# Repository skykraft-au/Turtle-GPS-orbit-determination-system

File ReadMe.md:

# Overview
The Turtle GPS is an open-source, cost-effective, low-power, and low-weight solution to orbit determination. The device resolves the issues faced by standard tracking methods such as radar while democratising space by making tracking cooperative and community-based. The device satisfies CoCom regulations by being post-processed and non-continuous; instead, it beacons GPS data over LoRa packets at specified intervals.

The device is highly configurable through the FPGA Verilog code; see the configuration section below for more information.

Further development on the device is needed; the community is welcome to contribute to this. Information on directions for this development can be found in the Todo section below.

## Note regarding Turtle GPS v2.0
Note that the Turtle GPS v2.0 does not work by default, as there are issues regarding the flash and power supply components on the board; these issues are resolved in version 2.1. If you wish to use version 2.0, you will need to resolve these issues. The key issues and solutions are as follows:
- There are missing pull-up resistors on pins 1, 3, and 7 of the Flash memory; these should be 10 kΩ.
- The pull-up resistors on the M0, M1, and M2 pins on the underside of the FPGA are 10 kΩ, but they should be 1 kΩ to initiate the correct startup configuration.
- A few issues exist in the lower half of the power supply, including incorrect placement of the boost converter, sensitive output of the first 3.3 V LDO, and insufficient current rating in both the diode and boost converter. To resolve this, I recommend bypassing this section by powering the board with 3.3 V through test point 3.
- The done indicator pin from the FPGA should be a pull-up and not a pull-down.

# Todo
- GPS v2.1: Resolve issues with v2.0, update FPGA clock to an LVCMOS TCXO, tune LoRa RF path to between 401 MHz and 403 MHz.
- Update code to default the LoRa frequency to 401 MHz to 403 MHz and cascade the FIR to allow for a sharper cutoff to be attained with the limited FPGA resources.
- Program LoRa receiving capabilities into the FPGA to allow for remote shutdown with a unique user-defined code.
- Optimise size, weight, and performance of the device
- Test in orbit
- Set up a public website for uploading and processing of data
- Add satellite ID code generator and logger to the website

# Configuration of the Device
By default, the packets transmitted over LoRa are 512 bits wide and include a unique, user-defined satellite ID Code, packet index, user-defined bits, and the actual data.
| Number of Bits | Bit Locations | Purpose |
| -------------- | ------------- | ------- |
| 24 | \[512:489\] | Satellite ID Code |
| 12 | \[488:477\] | Packet Index |
| 28 | \[476:449\] | User-defined bits |
| 448 | \[448:0\] | GPS IQ Data |

The user-defined bits can be configured by changing the value of the respective register in the Verilog code. The configuration of the MAX2771 GNSS Receiver and the LoRa SX1276 can be changed by adjusting the values of their respective configuration registers in the MAX_Driver and LORA_Driver Verilog modules, respectively.

The total transmission size, as well as the sample size and whether samples are continuous or not, can all be configured through the value of the GPS_Config register in the GPS_Top Verilog module. Comments are included in the code to assist users with this.

# Licensing

This repository contains material under multiple licenses.

## Hardware

The hardware design files are licensed under CERN-OHL-P v2.

This includes:
- GPS v2.0/KiCad PCB/

## HDL and Software

The HDL and software source code are licensed under the MIT License.

This includes:
- GPS v2.0/Software and HDL/

## Documentation

Documentation, diagrams, and images are licensed under
Creative Commons Attribution 4.0 International (CC BY 4.0).

This includes:
- GPS v2.0/BoM/

A copy of each license is available in the licenses/ directory.

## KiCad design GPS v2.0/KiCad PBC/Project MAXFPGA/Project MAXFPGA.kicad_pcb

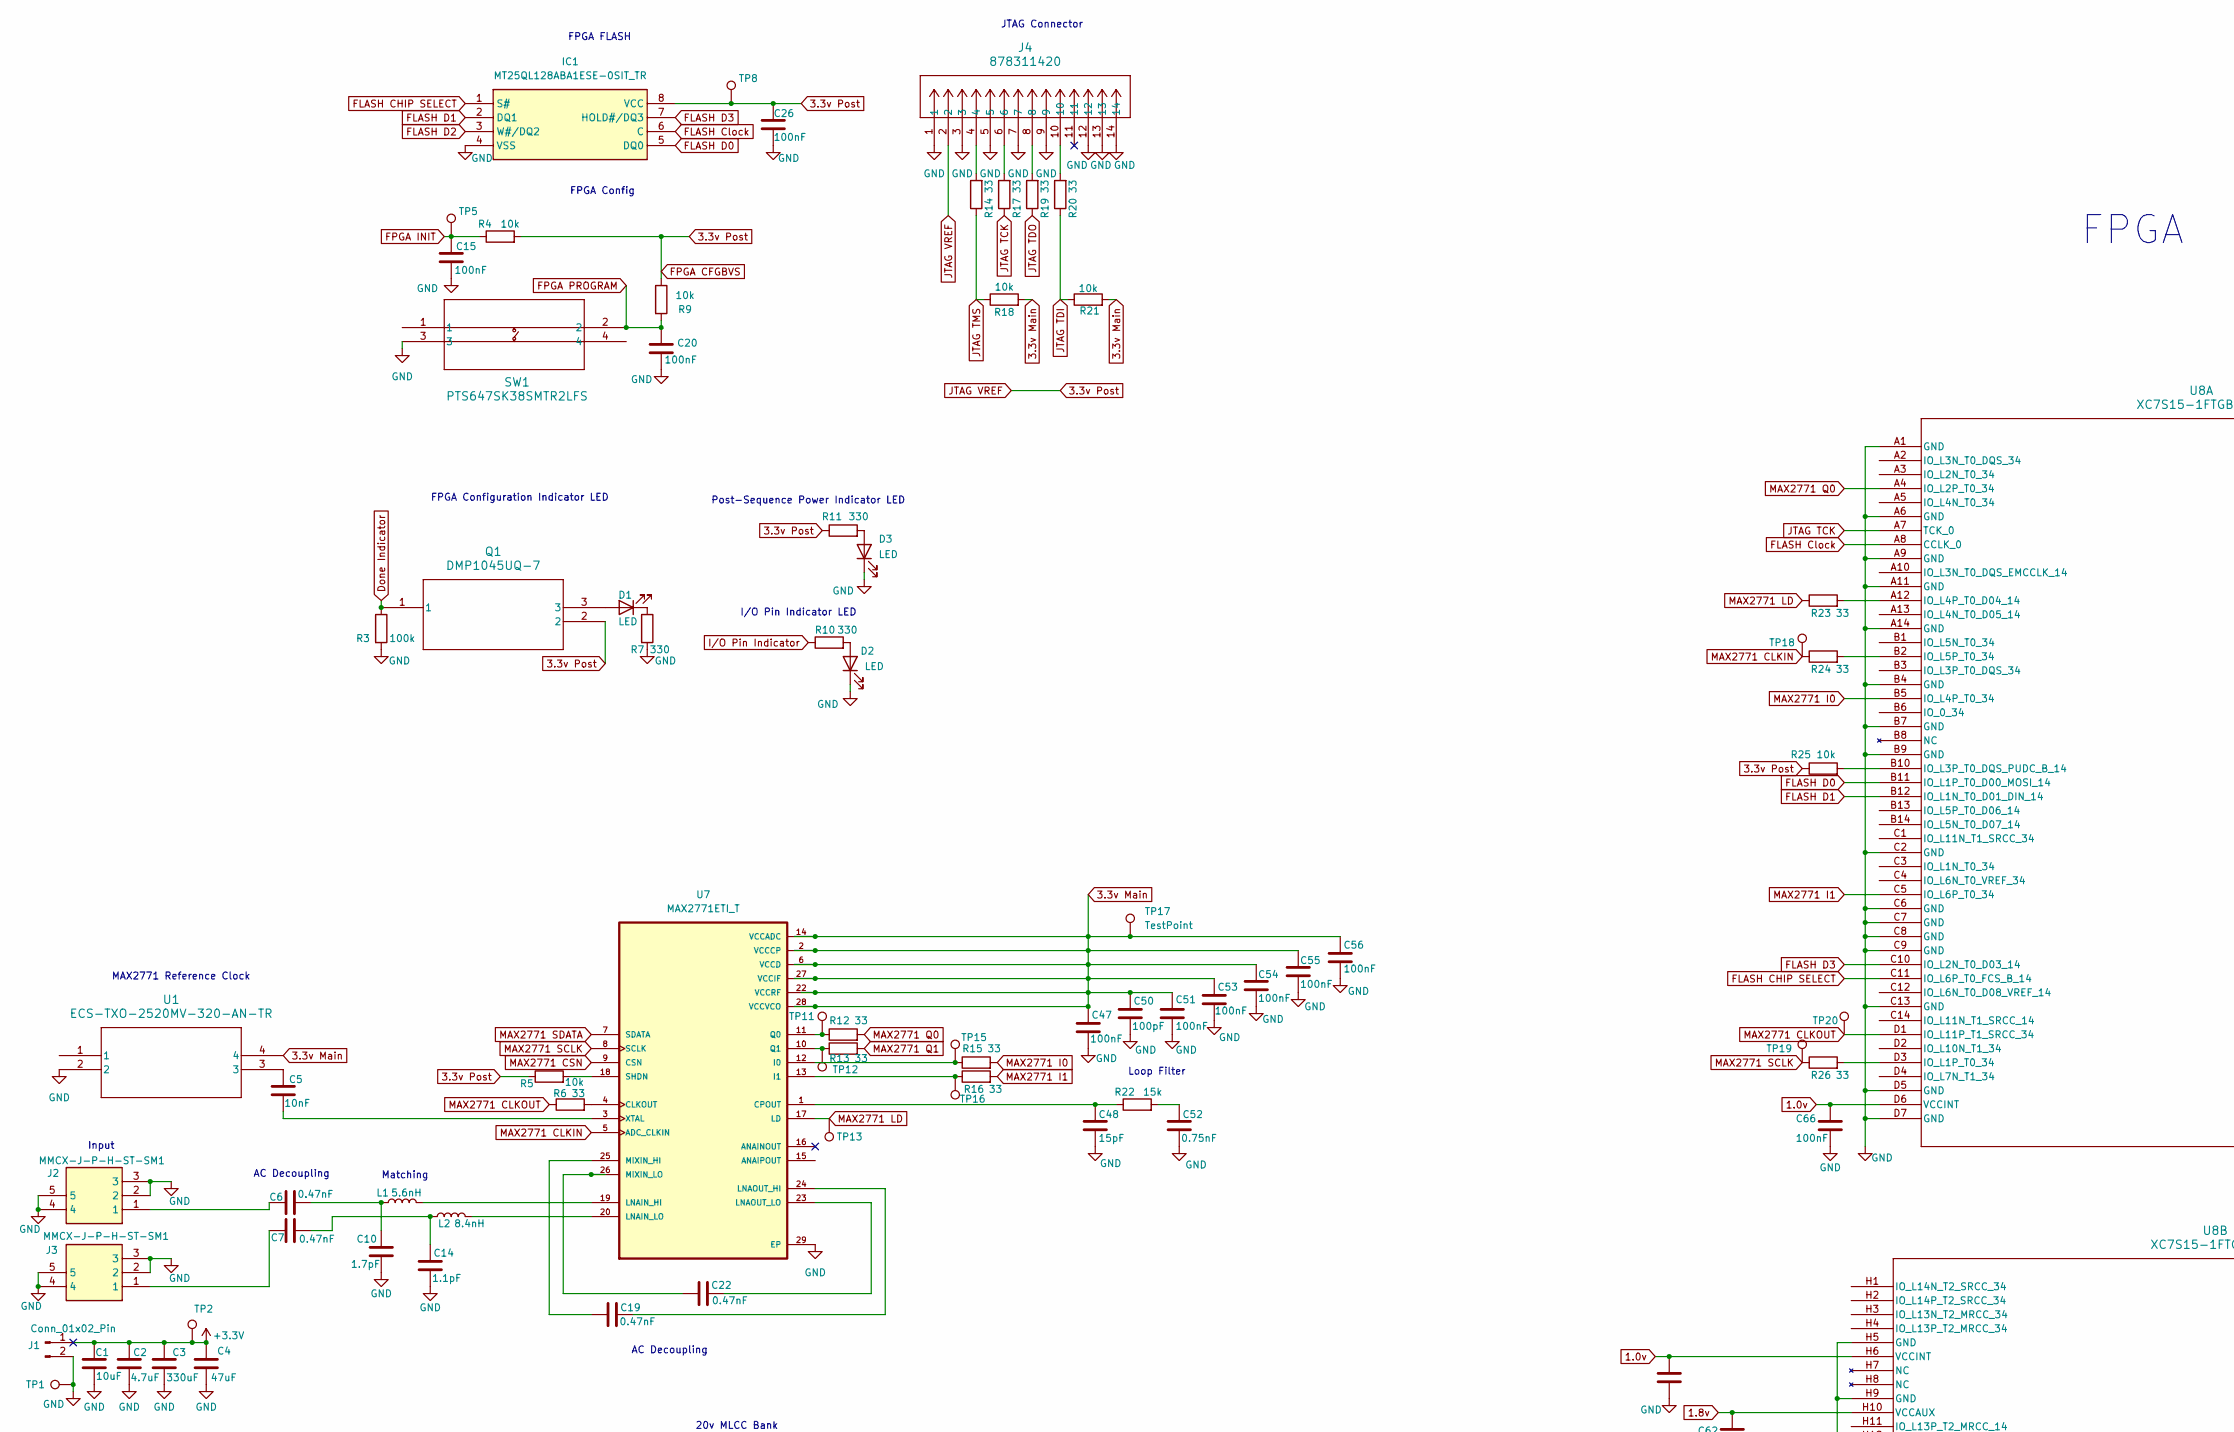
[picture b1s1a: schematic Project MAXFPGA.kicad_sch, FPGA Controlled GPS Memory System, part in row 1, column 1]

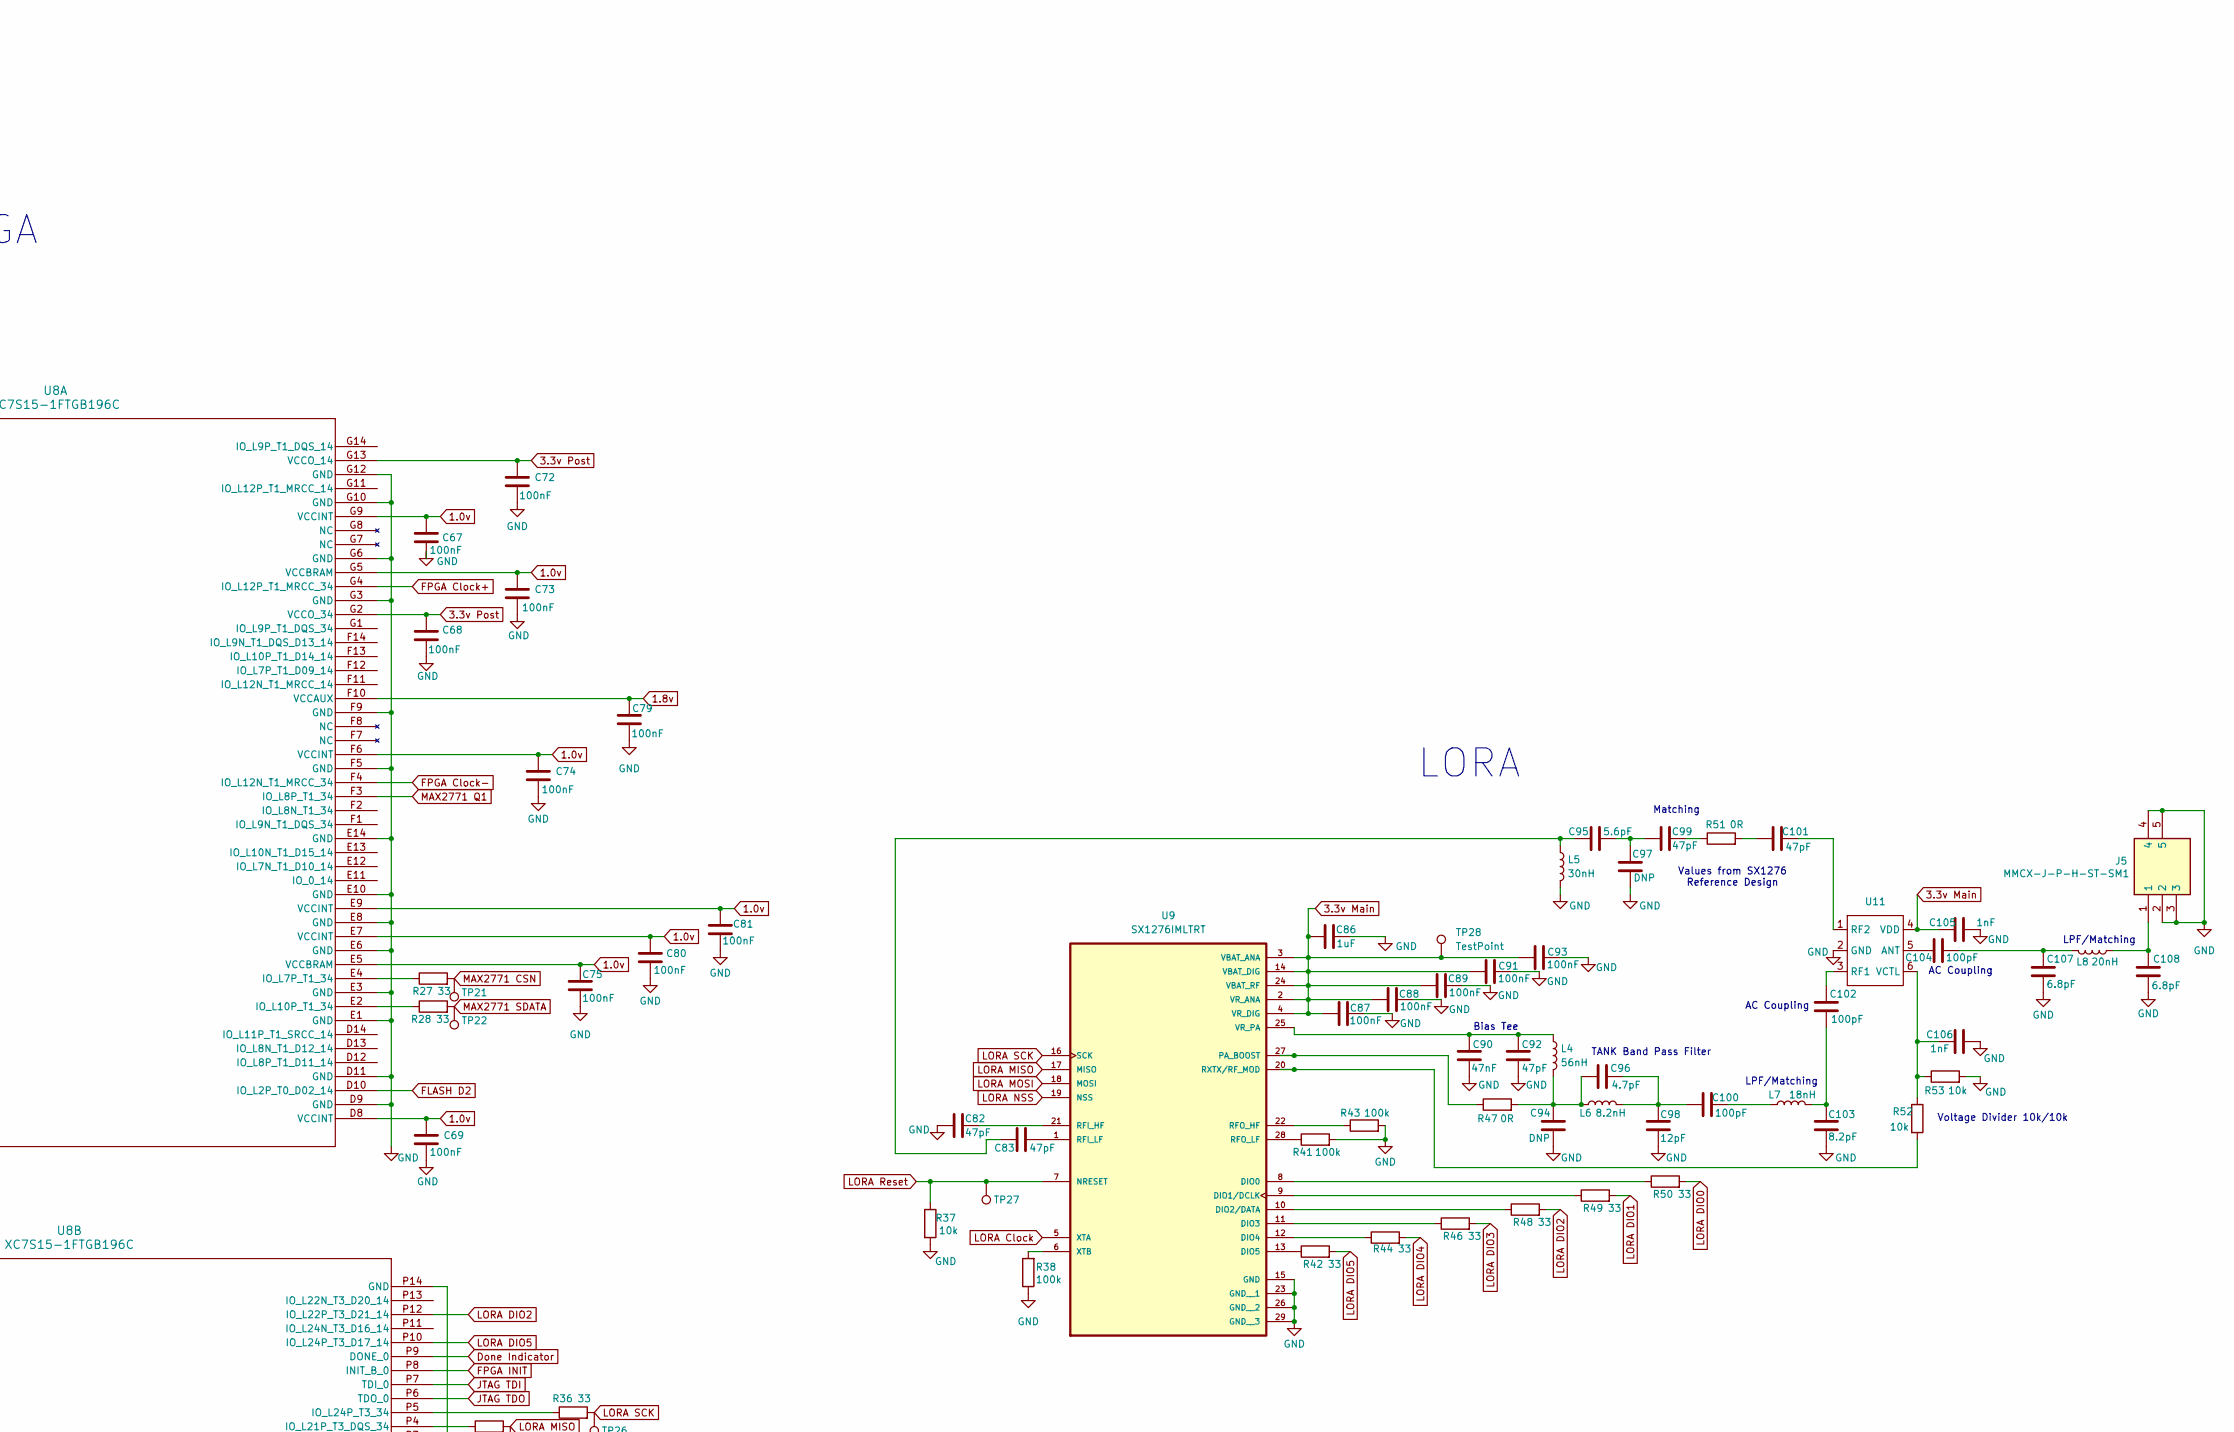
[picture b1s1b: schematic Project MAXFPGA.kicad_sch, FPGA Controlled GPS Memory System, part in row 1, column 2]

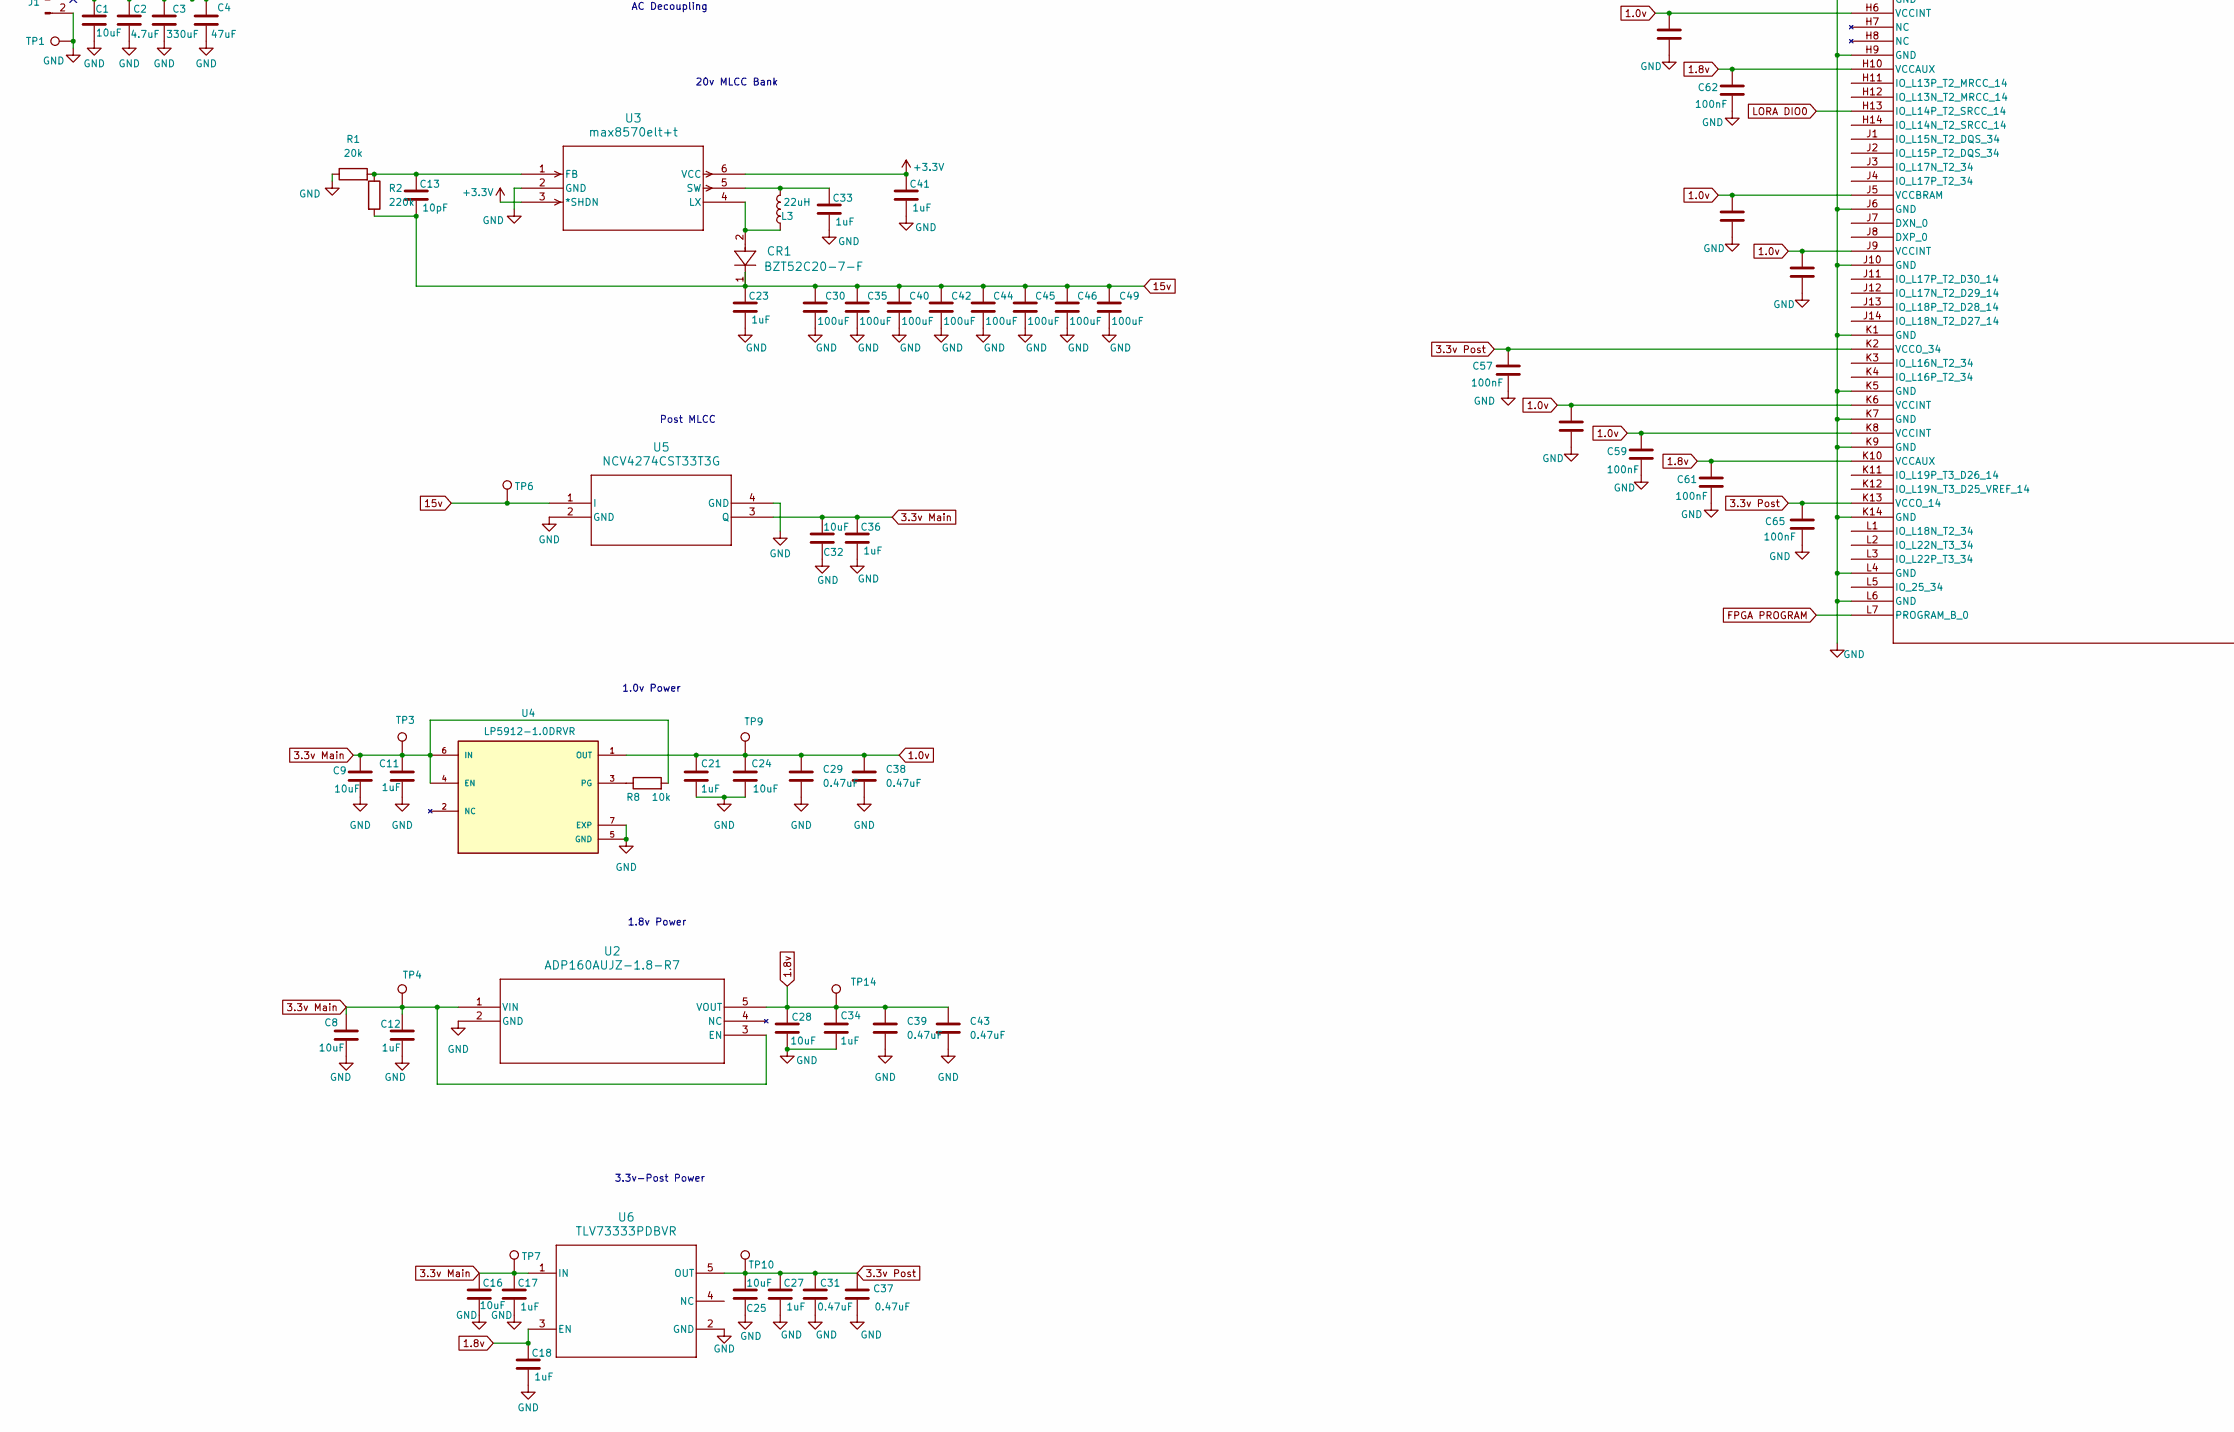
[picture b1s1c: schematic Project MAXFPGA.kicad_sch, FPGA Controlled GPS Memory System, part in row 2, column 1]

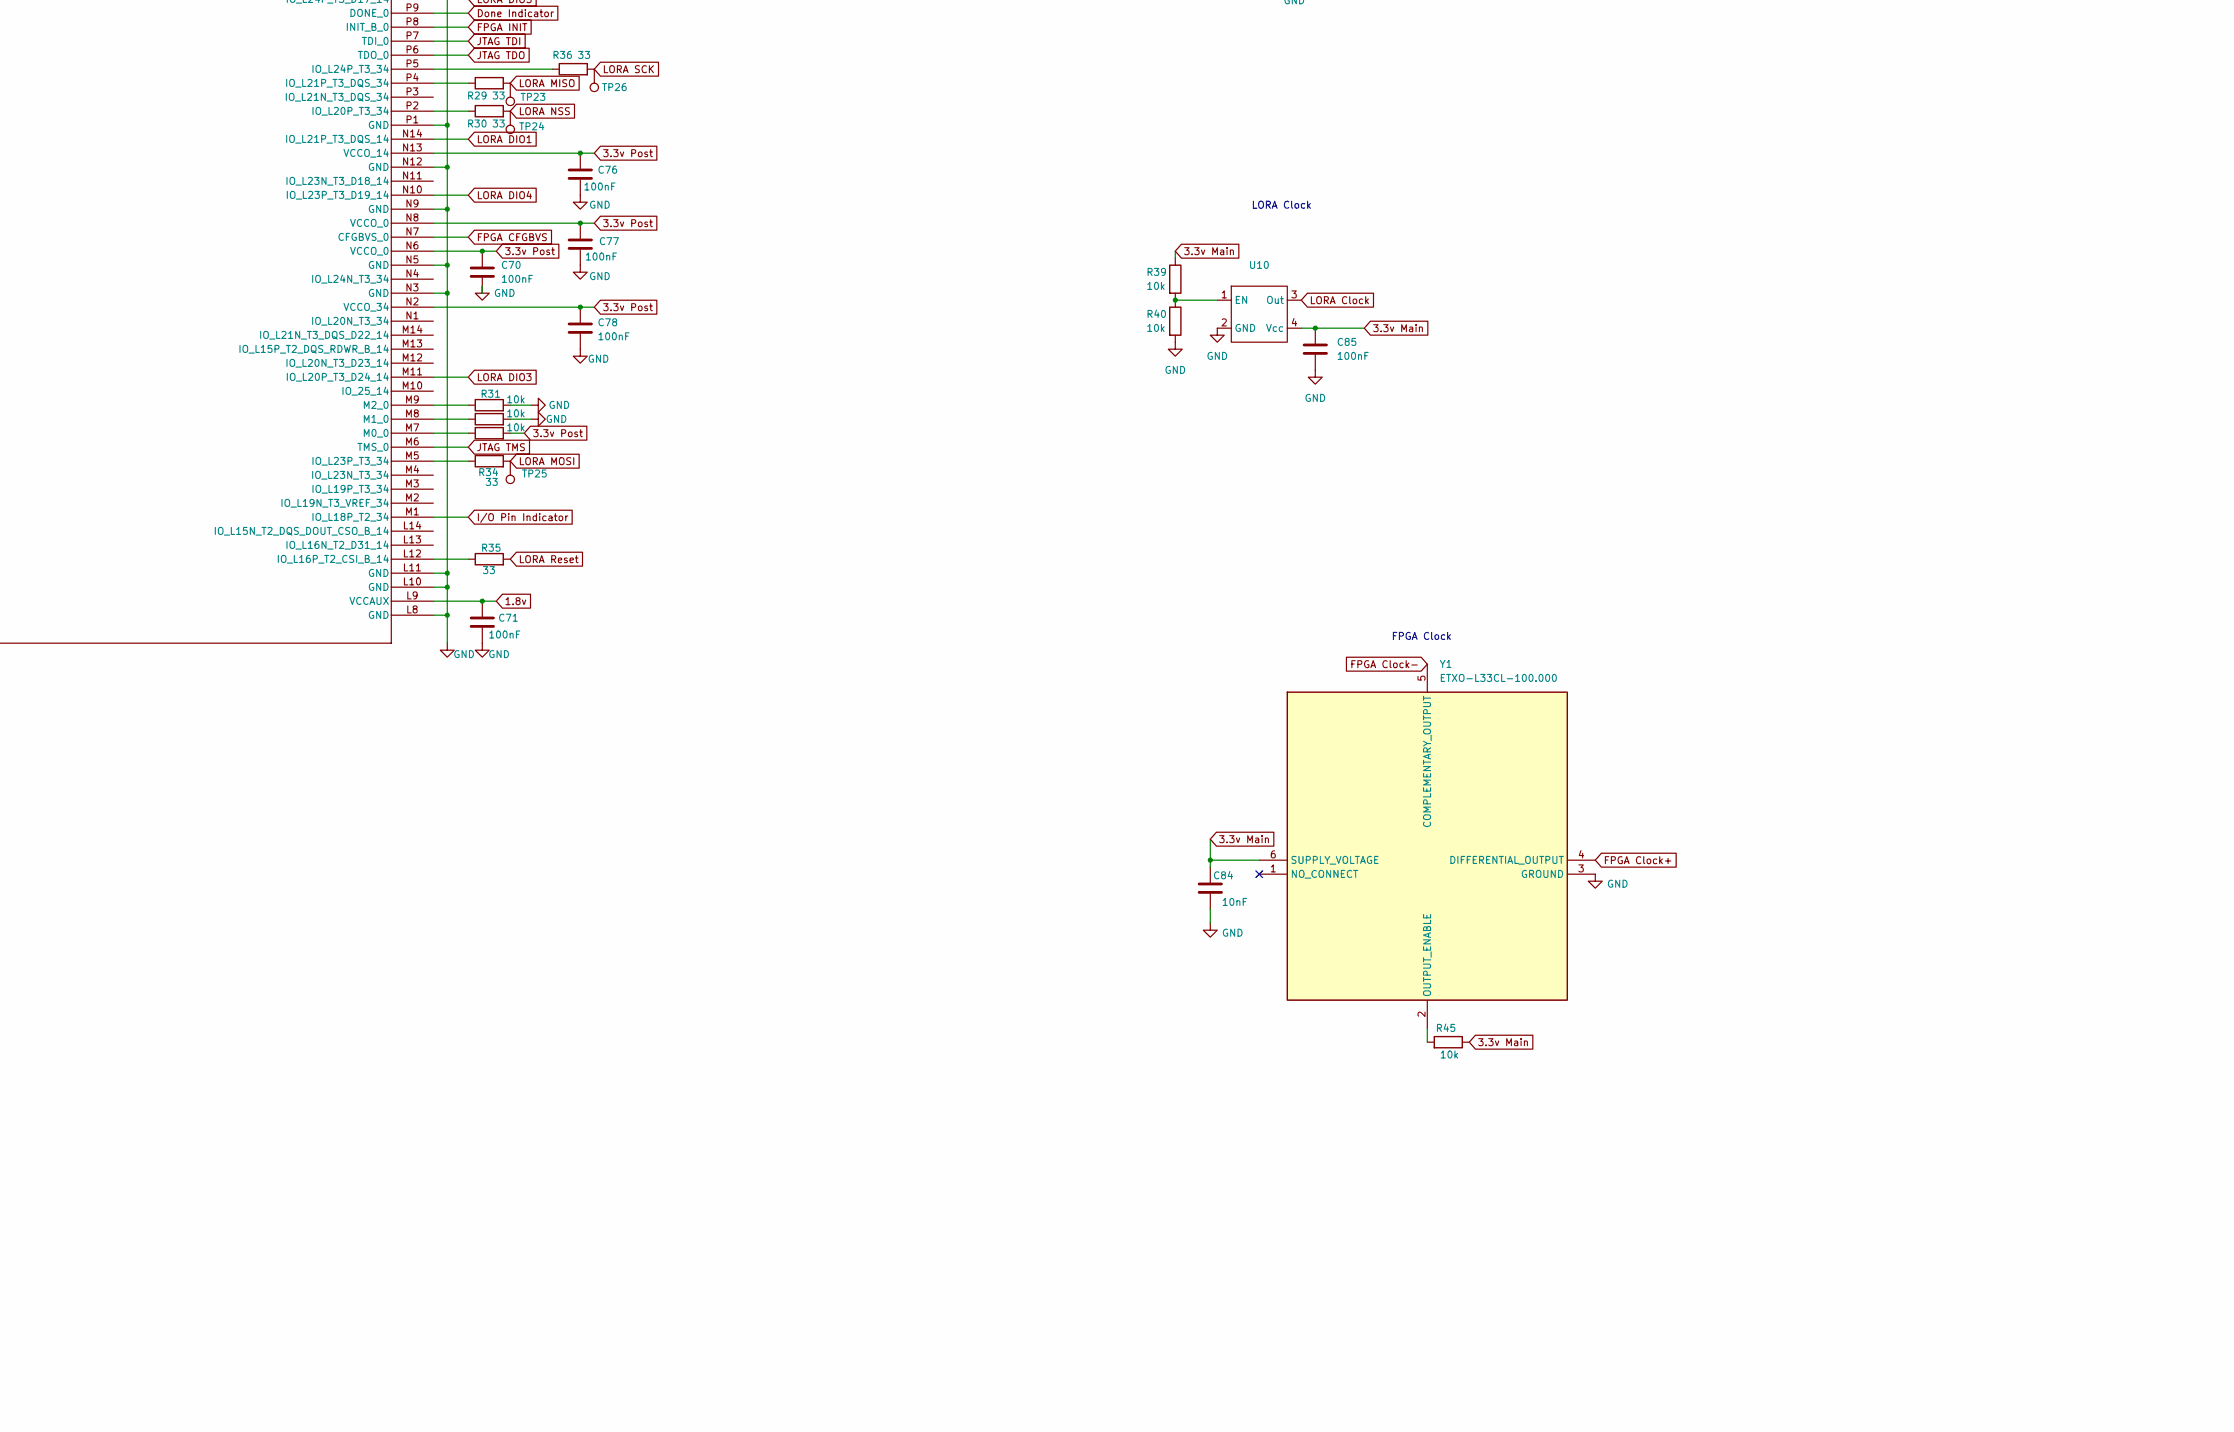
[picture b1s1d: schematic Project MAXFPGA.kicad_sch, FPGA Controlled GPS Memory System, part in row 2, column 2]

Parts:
C1, C8, C9, C16, C24, C25, C28, C32: 10uF; C_0402_1005Metric
C2: 4.7uF; C_0402_1005Metric
C3: 330uF; C_1210_3225Metric
C4: 47uF; C_1206_3216Metric
C5, C84: 10nF; C_0402_1005Metric
C6, C7, C19, C22: 0.47nF; C_0402_1005Metric
C10: 1.7pF; C_0402_1005Metric
C11, C12, C17, C18, C21, C23, C27, C33, C34, C36, C41, C86: 1uF; C_0402_1005Metric
C13: 10pF; C_0402_1005Metric
C14: 1.1pF; C_0402_1005Metric
C15, C20, C57, C58, C59, C60, C61, C62, C63, C64, C65, C66, C67, C68, C69, C70, C71, C72, C73, C74, C75, C76, C77, C78, C79, C80, C81: 100nF; CAPC0603X33N_1
C26, C47, C51, C53, C54, C55, C56, C85, C87, C88, C89, C91, C93: 100nF; C_0402_1005Metric
C29, C31, C37, C38, C39, C43: 0.47uF; C_0402_1005Metric
C30, C35, C40, C42, C44, C45, C46, C49: 100uF; C_1210_3225Metric
C48: 15pF; CAPC17595_87N_KEM
C50, C100, C102, C104: 100pF; C_0402_1005Metric
C52: 0.75nF; C_0402_1005Metric
C82, C83, C92, C99, C101: 47pF; C_0402_1005Metric
C90: 47nF; C_0402_1005Metric
C94, C97: DNP; C_0402_1005Metric
C95: 5.6pF; C_0402_1005Metric
C96: 4.7pF; C_0402_1005Metric
C98: 12pF; C_0402_1005Metric
C103: 8.2pF; C_0402_1005Metric
C105, C106: 1nF; C_0402_1005Metric
C107, C108: 6.8pF; C_0402_1005Metric
CR1: BZT52C20-7-F; D_SOD-128
D1, D2, D3: LED; LED_SML-D12U1WT86
IC1: MT25QL128ABA1ESE-0SIT_TR; SOIC127P790X216-8N; Mouser Part Number 340-224871-REEL
J1: Conn_01x02_Pin; CONN2_M20-999_1x2_HRW
J2, J3, J5: MMCX-J-P-H-ST-SM1; MMCXJPHSTSM1; Mouser Part Number 200-MMCXJPHSTSM1
J4: 878311420; JTAG_Conn
L1: 5.6nH; INDC1006X60N_2
L2: 8.4nH; INDC1006X60N
L3: 22uH; L_0805_2012Metric
L4: 56nH; INDC1005X60N
L5: 30nH; INDC1006X60N_5
L6: 8.2nH; INDC1006X60N_3
L7: 18nH; INDC1006X60N_5
L8: 20nH; INDC1006X60N_4
Q1: DMP1045UQ-7; DONE_FET
R1: 20k; R_0402_1005Metric
R2: 220k; R_0402_1005Metric
R3: 100k; RESC1005X40N_5
R4, R5, R8, R9, R18, R21, R25, R31, R32, R33, R37, R39, R40, R45, R52, R53: 10k; RESC1005X40N_3
R6, R12, R13, R14, R15, R16, R17, R19, R20, R23, R24, R26, R27, R28, R29, R30, R34, R35, R36, R42, R44, R46, R48, R49, R50: 33; RESC1005X40N_2
R7, R10, R11: 330; RESC1005X40N_5
R22: 15k; RES_ERA2AEB153X
R38, R41, R43: 100k; RESC1005X40N_4
R47, R51: 0R; RESC1005X40N
SW1: PTS647SK38SMTR2LFS; PTS647SK38SMTR2LFS_CNK
TP1, TP2, TP3, TP4, TP5, TP6, TP7, TP8, TP9, TP10, TP11, TP12, TP13, TP14, TP15, TP16, TP17, TP18, TP19, TP20, TP21, TP22, TP23, TP24, TP25, TP26, TP27, TP28: TestPoint; TestPoint_Pad_1.0x1.0mm
U1: ECS-TXO-2520MV-320-AN-TR; SMD04_XTAL_2P5X2_ECS
U2: ADP160AUJZ-1.8-R7; 1.8V_REG
U3: max8570elt+t; 21-0164_L622&plus_1_MXM
U4: LP5912-1.0DRVR; SON65P200X200X80-7N; PARTREV D
U5: NCV4274CST33T3G; SOT-223_ONS
U6: TLV73333PDBVR; 3.3v_Reg
U7: MAX2771ETI_T; QFN50P500X500X80-29N
U8: XC7S15-1FTGB196C; FTGB196_AMD
U9: SX1276IMLTRT; QFN65P600X600X100-29N; PARTREV 5
U10: MP06838
U11: ASWD-S2-000
Y1: ETXO-L33CL-100.000; ETXOL33CL100000; Manufacturer_Part_Number ETXO-L33CL-100.000; Mouser Part Number 520-ETXO-L33CL-10000

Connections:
1.0v: C21.1, C24.1, C29.1, C38.1, C58.1, C59.1, C60.1, C63.1, C64.1, C66.2, C67.1, C69.1, C73.1, C74.1, C75.1, C80.1, C81.2, TP9.1 (1_1), U4.1 (OUT), U8.D6 (VCCINT), U8.D8 (VCCINT), U8.E5 (VCCBRAM), U8.E7 (VCCINT), U8.E9 (VCCINT), U8.F6 (VCCINT), U8.G5 (VCCBRAM), U8.G9 (VCCINT), U8.H6 (VCCINT), U8.J5 (VCCBRAM), U8.J9 (VCCINT), U8.K6 (VCCINT), U8.K8 (VCCINT)
1.8v: C18.1, C28.2, C34.2, C39.1, C43.1, C61.2, C62.1, C71.2, C79.2, TP14.1 (1_1), U2.5 (VOUT), U6.3 (EN), U8.F10 (VCCAUX), U8.H10 (VCCAUX), U8.K10 (VCCAUX), U8.L9 (VCCAUX)
3.3v Main: C8.1, C9.1, C11.1, C12.1, C16.1, C17.1, C32.1, C36.1, C47.1, C50.1, C51.1, C53.1, C54.1, C55.1, C56.1, C84.1, C85.1, C86.1, C87.1, C88.1, C89.1, C91.1, C93.1, C105.1, R8.2, R18.2, R21.2, R39.1, R45.1, TP3.1 (1_1), TP4.1 (1_1), TP7.1 (1_1), TP17.1 (1_1), TP28.1 (1_1), U1.4, U2.1 (VIN), U2.3 (EN), U4.4 (EN), U4.6 (IN), U5.3 (Q), U6.1 (IN), U7.2 (VCCCP), U7.6 (VCCD), U7.14 (VCCADC), U7.22 (VCCRF), U7.27 (VCCIF), U7.28 (VCCVCO), U9.2 (VR_ANA), U9.3 (VBAT_ANA), U9.4 (VR_DIG), U9.14 (VBAT_DIG), U9.24 (VBAT_RF), U10.4 (Vcc), U11.4 (VDD), Y1.6 (SUPPLY_VOLTAGE)
3.3v Post: C25.1, C26.1, C27.1, C31.1, C37.1, C57.1, C65.1, C68.1, C70.1, C72.1, C76.1, C77.1, C78.1, IC1.8 (VCC), J4.2, Q1.2, R4.2, R5.1, R9.1, R11.1, R25.1, R33.2, TP8.1 (1_1), TP10.1 (1_1), U6.5 (OUT), U8.G2 (VCCO_34), U8.G13 (VCCO_14), U8.K2 (VCCO_34), U8.K13 (VCCO_14), U8.N2 (VCCO_34), U8.N6 (VCCO_0), U8.N7 (CFGBVS_0), U8.N8 (VCCO_0), U8.N13 (VCCO_14); also elsewhere on the board
15v: C13.2, C23.1, C30.2, C35.2, C40.2, C42.2, C44.2, C45.2, C46.2, C49.2, CR1.1, R2.2, TP6.1 (1_1), U5.1 (I)
+3.3V: C1.2, C2.2, C3.2, C4.2, C41.1, J1.1, TP2.1 (1_1), U3.3 (*SHDN), U3.6 (VCC); also elsewhere on the board
Done Indicator: Q1.1, R3.1, U8.P9 (DONE_0)
FLASH CHIP SELECT: IC1.1 (S#), U8.C11 (IO_L6P_T0_FCS_B_14); also elsewhere on the board
FLASH Clock: IC1.6 (C), U8.A8 (CCLK_0); also elsewhere on the board
FLASH D0: IC1.5 (DQ0), U8.B11 (IO_L1P_T0_D00_MOSI_14); also elsewhere on the board
FLASH D1: IC1.2 (DQ1), U8.B12 (IO_L1N_T0_D01_DIN_14); also elsewhere on the board
FLASH D2: IC1.3 (W#/DQ2), U8.D10 (IO_L2P_T0_D02_14); also elsewhere on the board
FLASH D3: IC1.7 (HOLD#/DQ3), U8.C10 (IO_L2N_T0_D03_14); also elsewhere on the board
FPGA Clock+: U8.G4 (IO_L12P_T1_MRCC_34), Y1.4 (DIFFERENTIAL_OUTPUT)
FPGA Clock-: U8.F4 (IO_L12N_T1_MRCC_34), Y1.5 (COMPLEMENTARY_OUTPUT)
FPGA INIT: C15.1, R4.1, TP5.1 (1_1), U8.P8 (INIT_B_0)
FPGA PROGRAM: C20.1, R9.2, SW1.2, U8.L7 (PROGRAM_B_0); also elsewhere on the board
GND: C1.1, C2.1, C3.1, C4.1, C8.2, C9.2, C10.2, C11.2, C12.2, C14.2, C15.2, C16.2, C17.2, C18.2, C20.2, C21.2, C23.2, C24.2, C25.2, C26.2, C27.2, C28.1, C29.2, C30.1, C31.2, C32.2, C33.2, C34.1, C35.1, C36.2, C37.2, C38.2, C39.2, C40.1, C41.2, C42.1, C43.2, C44.1, C45.1, C46.1, C47.2, C48.2, C49.1, C50.2, C51.2, C52.2, C53.2, C54.2, C55.2, C56.2, C57.2, C58.2, C59.2, C60.2, C61.1, C62.2, C63.2, C64.2, C65.2, C66.1, C67.2, C68.2, C69.2, C70.2, C71.1, C72.2, C73.2, C74.2, C75.2, C76.2, C77.2, C78.2, C79.1, C80.2, C81.1, C82.1, C84.2, C85.2, C86.2, C87.2, C88.2, C89.2, C90.2, C91.2, C92.2, C93.2, C94.2, C97.2, C98.2, C103.2, C105.2, C106.2, C107.2, C108.2, D2.1 (K), D3.1 (K), IC1.4 (VSS), J1.2, J2.2, J2.3, J2.4, J2.5, J3.2, J3.3, J3.4, J3.5, J4.1, J4.3, J4.5, J4.7, J4.9, J4.12, J4.13, J4.14, J5.2, J5.3, J5.4, J5.5, L5.2, R1.1, R3.2, R7.2, R31.2, R32.2, R37.2, R38.1, R40.2, R41.2, R43.2, R53.2, SW1.3, TP1.1 (1_1), U1.2, U2.2 (GND), U3.2 (GND), U4.5 (GND), U4.7 (EXP), U5.2 (GND), U5.4 (GND), U6.2 (GND), U7.29 (EP), U8.A1 (GND), U8.A6 (GND), U8.A9 (GND), U8.A11 (GND), U8.A14 (GND), U8.B4 (GND), U8.B7 (GND), U8.B9 (GND), U8.C2 (GND), U8.C6 (GND), U8.C7 (GND), U8.C8 (GND), U8.C9 (GND), U8.C13 (GND), U8.D5 (GND), U8.D7 (GND), U8.D9 (GND), U8.D11 (GND), U8.E1 (GND), U8.E3 (GND), U8.E6 (GND), U8.E8 (GND), U8.E10 (GND), U8.E14 (GND), U8.F5 (GND), U8.F9 (GND), U8.G3 (GND), U8.G6 (GND), U8.G10 (GND), U8.G12 (GND), U8.H5 (GND), U8.H9 (GND), U8.J6 (GND), U8.J10 (GND), U8.K1 (GND), U8.K5 (GND), U8.K7 (GND), U8.K9 (GND), U8.K14 (GND), U8.L4 (GND), U8.L6 (GND), U8.L8 (GND), U8.L10 (GND), U8.L11 (GND), U8.N3 (GND), U8.N5 (GND), U8.N9 (GND), U8.N12 (GND), U8.P1 (GND), U8.P14 (GND), U9.15 (GND), U9.23 (GND__1), U9.26 (GND__2), U9.29 (GND__3), U10.2 (GND), U11.2 (GND), Y1.3 (GROUND); also elsewhere on the board
I/O Pin Indicator: R10.1, U8.M1 (IO_L18P_T2_34)
JTAG TCK: R17.1, U8.A7 (TCK_0)
JTAG TDI: R20.1, R21.1, U8.P7 (TDI_0)
JTAG TDO: R19.1, U8.P6 (TDO_0)
JTAG TMS: R14.1, R18.1, U8.M6 (TMS_0)
LORA Clock: U9.5 (XTA), U10.3 (Out)
LORA DIO0: R50.2, U8.H13 (IO_L14P_T2_SRCC_14)
LORA DIO1: R49.2, U8.N14 (IO_L21P_T3_DQS_14)
LORA DIO2: R48.2, U8.P12 (IO_L22P_T3_D21_14)
LORA DIO3: R46.2, U8.M11 (IO_L20P_T3_D24_14)
LORA DIO4: R44.2, U8.N10 (IO_L23P_T3_D19_14)
LORA DIO5: R42.2, U8.P10 (IO_L24P_T3_D17_14)
LORA MISO: R29.2, TP23.1 (1_1), U9.17 (MISO)
LORA MOSI: R34.2, TP25.1 (1_1), U9.18 (MOSI)
LORA NSS: R30.2, TP24.1 (1_1), U9.19 (NSS)
LORA Reset: R35.2, R37.1, TP27.1 (1_1), U9.7 (NRESET)
LORA SCK: R36.2, TP26.1 (1_1), U9.16 (SCK)
MAX2771 CLKIN: R24.1, TP18.1 (1_1), U7.5 (ADC_CLKIN)
MAX2771 CLKOUT: R6.1, TP20.1 (1_1), U8.D1 (IO_L11P_T1_SRCC_34)
MAX2771 CSN: R27.2, TP21.1 (1_1), U7.9 (CSN)
MAX2771 I0: R15.2, U8.B5 (IO_L4P_T0_34)
MAX2771 I1: R16.2, U8.C5 (IO_L6P_T0_34)
MAX2771 LD: R23.1, TP13.1 (1_1), U7.17 (LD)
MAX2771 Q0: R12.2, U8.A4 (IO_L2P_T0_34)
MAX2771 Q1: R13.2, U8.F3 (IO_L8P_T1_34)
MAX2771 SCLK: R26.1, TP19.1 (1_1), U7.8 (SCLK)
MAX2771 SDATA: R28.2, TP22.1 (1_1), U7.7 (SDATA)
unnamed: C5.2, U1.3
unnamed 46: C6.1, J2.1; also elsewhere on the board
unnamed 47: C7.1, J3.1; also elsewhere on the board
unnamed: C6.2, C10.1, L1.1
unnamed: C7.2, C14.1, L2.1
unnamed: C52.1, R22.2
unnamed: C83.1, C95.1, L5.1
unnamed: C94.1, C96.1, L4.2, L6.1, R47.2
unnamed: C95.2, C97.1, C99.1
unnamed: C99.2, R51.1
unnamed: C96.2, C98.1, C100.1, L6.2
unnamed: C100.2, L7.1
unnamed: C101.1, R51.2
unnamed: C102.2, C103.1, L7.2
unnamed: C104.2, C107.1, L8.2
unnamed 60: C108.1, J5.1, L8.1; also elsewhere on the board
unnamed: D1.2 (A), Q1.3
unnamed: D1.1 (K), R7.1
unnamed: D2.2 (A), R10.2
unnamed: D3.2 (A), R11.2
unnamed 65: J4.4, R14.2; also elsewhere on the board
unnamed 66: J4.6, R17.2; also elsewhere on the board
unnamed 67: J4.8, R19.2; also elsewhere on the board
unnamed 68: J4.10, R20.2; also elsewhere on the board
unnamed: C13.1, R1.2, R2.1, U3.1 (FB)
unnamed: CR1.2, L3.1, U3.4 (LX)
unnamed: C33.1, L3.2, U3.5 (SW)
unnamed: R8.1, U4.3 (PG)
unnamed: R6.2, U7.4 (CLKOUT)
unnamed: C48.1, R22.1, U7.1 (CPOUT)
unnamed: R15.1, TP15.1 (1_1), U7.12 (I0)
unnamed: R16.1, TP16.1 (1_1), U7.13 (I1)
unnamed: L1.2, U7.19 (LNAIN_HI)
unnamed: L2.2, U7.20 (LNAIN_LO)
unnamed: C19.2, U7.24 (LNAOUT_HI)
unnamed: C22.2, U7.23 (LNAOUT_LO)
unnamed: C19.1, U7.25 (MIXIN_HI)
unnamed: C22.1, U7.26 (MIXIN_LO)
unnamed: R12.1, TP11.1 (1_1), U7.11 (Q0)
unnamed: R13.1, TP12.1 (1_1), U7.10 (Q1)
unnamed: R5.2, U7.18 (SHDN)
unnamed: C5.1, U7.3 (XTAL)
unnamed: R26.2, U8.D3 (IO_L1P_T0_34)
unnamed: R25.2, U8.B10 (IO_L3P_T0_DQS_PUDC_B_14)
unnamed: R23.2, U8.A12 (IO_L4P_T0_D04_14)
unnamed: R24.2, U8.B2 (IO_L5P_T0_34)
unnamed: R27.1, U8.E4 (IO_L7P_T1_34)
unnamed: R28.1, U8.E2 (IO_L10P_T1_34)
unnamed: R35.1, U8.L12 (IO_L16P_T2_CSI_B_14)
unnamed: R30.1, U8.P2 (IO_L20P_T3_34)
unnamed: R29.1, U8.P4 (IO_L21P_T3_DQS_34)
unnamed: R34.1, U8.M5 (IO_L23P_T3_34)
unnamed: R36.1, U8.P5 (IO_L24P_T3_34)
unnamed: R33.1, U8.M7 (M0_0)
unnamed: R32.1, U8.M8 (M1_0)
unnamed: R31.1, U8.M9 (M2_0)
unnamed: R50.1, U9.8 (DIO0)
unnamed: R49.1, U9.9 (DIO1/DCLK)
unnamed: R48.1, U9.10 (DIO2/DATA)
unnamed: R46.1, U9.11 (DIO3)
unnamed: R44.1, U9.12 (DIO4)
unnamed: R42.1, U9.13 (DIO5)
unnamed: R47.1, U9.27 (PA_BOOST)
unnamed: C82.2, U9.21 (RFI_HF)
unnamed: C83.2, U9.1 (RFI_LF)
unnamed: R43.1, U9.22 (RFO_HF)
unnamed: R41.1, U9.28 (RFO_LF)
unnamed: R52.2, U9.20 (RXTX/RF_MOD)
unnamed: C90.1, C92.1, L4.1, U9.25 (VR_PA)
unnamed: R38.2, U9.6 (XTB)
unnamed: R39.2, R40.1, U10.1 (EN)
unnamed: C104.1, U11.5 (ANT)
unnamed: C102.1, U11.3 (RF1)
unnamed: C101.2, U11.1 (RF2)
unnamed: C106.1, R52.1, R53.1, U11.6 (VCTL)
unnamed: R45.2, Y1.2 (OUTPUT_ENABLE)

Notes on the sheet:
1.0v Power
Values from SX1276 Reference Design
Post-Sequence Power Indicator LED
FPGA FLASH
FPGA Config
LPF/Matching
Post MLCC
LORA Clock
TANK Band Pass Filter
20v MLCC Bank
FPGA
AC Decoupling
FPGA Clock
1.8v Power
I/O Pin Indicator LED
Input
FPGA Configuration Indicator LED
Matching
Matching
AC Coupling
Voltage Divider 10k/10k
3.3v-Post Power
JTAG Connector
Loop Filter
MAX2771 Reference Clock
Bias Tee
LORA
